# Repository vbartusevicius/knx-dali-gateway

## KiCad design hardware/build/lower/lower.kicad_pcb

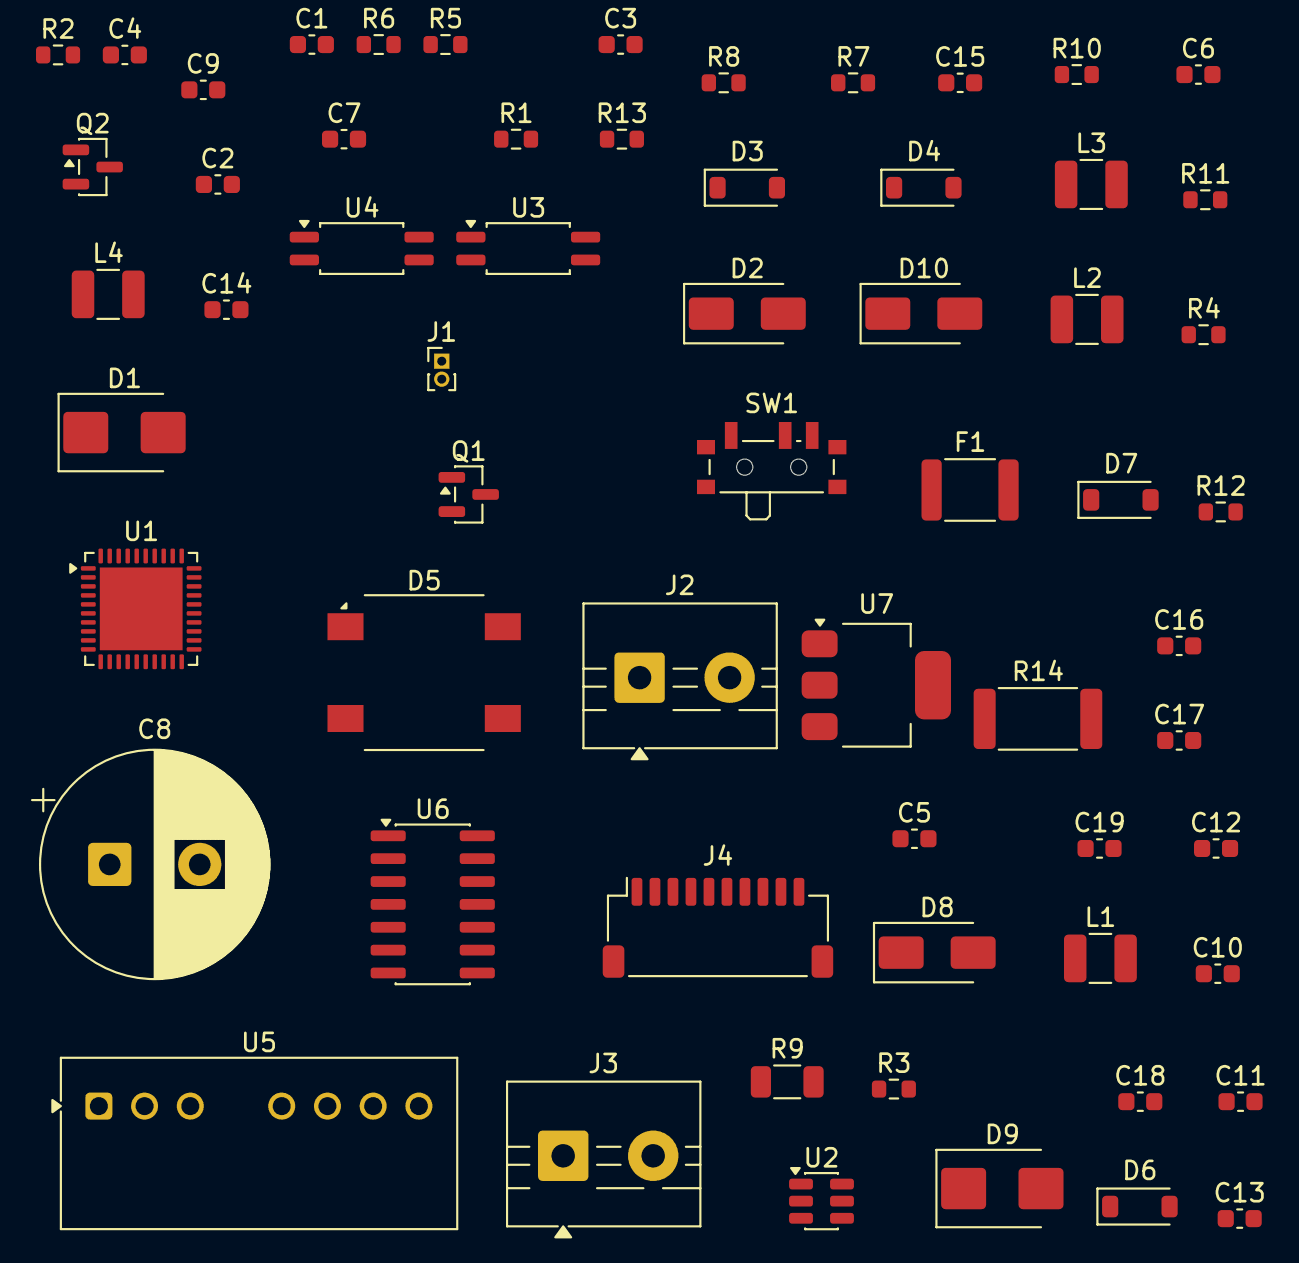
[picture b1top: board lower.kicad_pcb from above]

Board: 2 copper layers, 62 parts (0 on the bottom side), 46 nets, no tracks yet.

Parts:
C1, C3, C4: TBD; C_0603_1608Metric
C2, C6: TBD 1u; C_0603_1608Metric
C5, C16, C17, C18: TBD 10u; C_0603_1608Metric
C7: TBD 33u; C_0603_1608Metric
C8: 1000u 25V; CP_Radial_D12.5mm_P5.00mm
C9, C10, C12, C15: 100n; C_0603_1608Metric
C11: 10u; C_0603_1608Metric
C13, C14: 22u; C_0603_1608Metric
C19: TBD 100u; C_0603_1608Metric
D1: SMBJ33A TBD; D_SMB
D2, D8, D10: TBD 60V 1A; D_SMA
D3, D4: TBD 60V 1A; D_SOD-123
D5: TBD 600V 1A bridge; Diode_Bridge_Vishay_DFS
D6: TBD 12V; D_SOD-123
D7: TBD 8V2; D_SOD-123
D9: TBD ~36V; D_SMB
F1: TBD 250mA; Fuse_1812_4532Metric
J1: KNX bus terminal pins; PinHeader_1x02_P1.00mm_Vertical
J2: DALI; TerminalBlock_MaiXu_MX126-5.0-02P_1x02_P5.00mm
J3: AUX; TerminalBlock_MaiXu_MX126-5.0-02P_1x02_P5.00mm
J4: JST-SH 1x10; JST_SH_SM10B-SRSS-TB_1x10-1MP_P1.00mm_Horizontal
L1, L2: TBD 68uH; L_1210_3225Metric
L3: TBD 4.7uH; L_1210_3225Metric
L4: TBD 330uH; L_1210_3225Metric
Q1: TBD >=60V >=0.5A NMOS; SOT-23
Q2: TBD NPN; SOT-23
R1: TBD ~10k; R_0603_1608Metric
R2, R3, R12, R13: TBD; R_0603_1608Metric
R4: 100k; R_0603_1608Metric
R5: 1k; R_0603_1608Metric
R6, R11: 10k; R_0603_1608Metric
R7, R8: TBD 47k; R_0603_1608Metric
R9: 2R4 0.5W; R_1206_3216Metric
R10: TBD 10k; R_0603_1608Metric
R14: 5R 1W; R_2512_6332Metric
SW1: TBD slide SPDT; SW_SPDT_PCM12
U1: NCN5130MNTWG; QFN-40-1EP_6x6mm_P0.5mm_EP4.6x4.6mm
U2: AP63203WU-7; TSOT-23-6
U3, U4: TBD opto; SOP-4_4.4x2.6mm_P1.27mm
U5: TMR4-2425WI 24V->24V 4W iso; Converter_DCDC_TRACO_TMR4-xxxxWI_THT
U6: TBD LM2574HVM-ADJ; SOIC-14_3.9x8.7mm_P1.27mm
U7: TBD LM317; SOT-223-3_TabPin2

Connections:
+3V3_MCU: C13.1, C14.1, C15.1, J4.1, L3.2, R11.1, U2.1
+3V3_TRX: C7.1, L1.2, U1.19, U1.20, U1.29, U1.30, U1.40
+12V_STORE: C8.1, C9.1, C11.1, C12.1, L2.2, R2.1, R4.1, U1.12, U1.13, U2.3
AUX_FUSED: D8.1, F1.2
AUX_P: C16.1, D8.2, D9.2, U5.2
CAV: C2.1, U1.5
CCP: C1.1, U1.3
CCP_B: C1.2, U1.4
CEQ1: C3.1, U1.7
CEQ2: C4.1, U1.8
DA1: D5.3, J2.1, SW1.2
DA2: D5.4, J2.2
DALI_20V: C19.1, L4.2, R12.1, U7.3
DALI_FB6: R12.2, R13.1, U6.3
DALI_GATE: D6.1, Q1.1, Q2.3, R8.1, U3.3
DALI_ISO24V: C17.1, C18.1, U5.7, U6.10
DALI_RX: J4.7, R11.2, U4.4
DALI_SENSE: Q1.2, Q2.1, R9.1
DALI_SUPPLY_SW: R14.2, SW1.1, U7.1
DALI_TX: J4.6, R5.1, R6.1
DA_P: D5.1, Q1.3, R7.1, R10.1
GND: C2.2, C3.2, C4.2, C5.2, C6.2, C7.2, C8.2, C9.2, C11.2, C12.2, C13.2, C14.2, C15.2, D1.1, D3.1, D4.1, J1.2, J4.2, J4.5, J4.8, R1.2, R3.2, R6.2, U1.1, U1.2, U1.14, U1.18, U1.21, U1.23, U1.24, U1.25, U1.26, U1.31, U1.33, U2.4, U3.2, U4.3
GNDA: C16.2, D9.1, J3.2, U5.1
GNDD: C17.2, C18.2, C19.2, D5.2, D6.2, D10.1, Q2.2, R8.2, R9.2, R13.2, U4.2, U5.6, U6.4, U6.5, U6.6
INT_SPARE1: J4.9, U1.36
INT_SPARE2: J4.10, U1.37
KNX_P: D1.2, D2.2, J1.1
KNX_P_PROT: D2.1, U1.6
KNX_RXD: J4.4, U1.27
KNX_TXD: J4.3, U1.28
unnamed: R1.1, U1.38
unnamed: R4.2, U2.2
unnamed: C10.1, U2.6
unnamed: C10.2, L3.1, U2.5
unnamed: R5.2, U3.1
unnamed: R7.2, U3.4
unnamed: D7.1, R10.2
unnamed: D7.2, U4.1
unnamed: F1.1, J3.1
unnamed: D10.2, L4.1, U6.12
unnamed: R14.1, U7.2
V20V: C6.1, U1.10
VDD2MV: R2.2, R3.1, U1.11
VFILT: C5.1, U1.9, U1.16
VSW1: D3.2, L1.1, U1.17
VSW2: D4.2, L2.1, U1.15

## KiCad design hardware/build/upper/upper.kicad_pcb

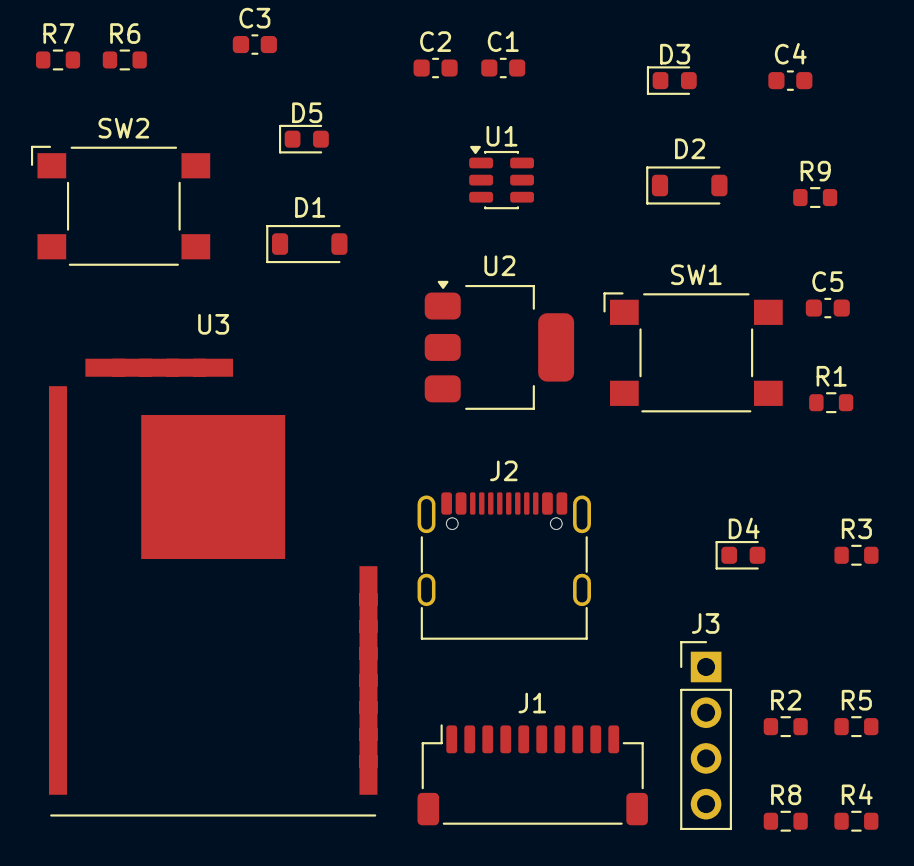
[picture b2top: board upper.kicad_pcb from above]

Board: 2 copper layers, 27 parts (0 on the bottom side), 22 nets, no tracks yet.

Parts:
C1, C5: 10u; C_0603_1608Metric
C2: 22u; C_0603_1608Metric
C3: 1u; C_0603_1608Metric
C4: 100n; C_0603_1608Metric
D1, D2: TBD 20V 1A; D_SOD-123
D3: red PROG; LED_0603_1608Metric
D4: green KNX; LED_0603_1608Metric
D5: yellow DALI; LED_0603_1608Metric
J1: JST-SH 1x10; JST_SH_SM10B-SRSS-TB_1x10-1MP_P1.00mm_Horizontal
J2: USB-C; USB_C_Receptacle_G-Switch_GT-USB-7010ASV
J3: OLED; PinHeader_1x04_P2.54mm_Vertical
R1, R2: 5.1k; R_0603_1608Metric
R3, R4: 10k; R_0603_1608Metric
R5, R6, R7: 1k; R_0603_1608Metric
R8, R9: 4.7k; R_0603_1608Metric
SW1: RESET; SW_SPST_Omron_B3FS-100xP
SW2: PROG; SW_SPST_Omron_B3FS-100xP
U1: TBD USB ESD; SOT-23-6
U2: TBD 3V3 LDO; SOT-223-3_TabPin2
U3: ESP32-C6-WROOM-1-N8; ESP32-C6-WROOM-1

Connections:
+3V3: C4.1, C5.1, D1.2, D2.2, J3.2, R3.1, R4.1, R8.1, R9.1, U3.2
+3V3_MCU: D2.1, J1.1
+3V3_USB: C2.1, D1.1, U2.2
+5V_USB: C1.1, J2.A4, J2.A9, J2.B4, J2.B9, U1.5, U2.3
DALI_RX: J1.7, U3.17
DALI_TX: J1.6, U3.16
EN: C3.1, R3.2, SW1.1, U3.3
GND: C1.2, C2.2, C3.2, C4.2, C5.2, D3.2, D4.2, D5.2, J1.2, J1.5, J1.8, J2.A1, J2.A12, J2.B1, J2.B12, J2.SH, J3.1, R1.2, R2.2, SW1.2, SW2.2, U1.2, U2.1, U3.1, U3.28, U3.29
I2C_SCL: J3.3, R9.2, U3.7
I2C_SDA: J3.4, R8.2, U3.6
INT_SPARE1: J1.9, U3.10
INT_SPARE2: J1.10, U3.9
KNX_RXD: J1.4, U3.19
KNX_TXD: J1.3, U3.18
unnamed: J2.A5, R1.1
unnamed: J2.B5, R2.1
unnamed: D3.1, R5.2
unnamed: D4.1, R6.2
unnamed: D5.1, R7.2
PROG_BTN: R4.2, SW2.1, U3.15
USB_DM: J2.A7, J2.B7, U1.1
USB_DP: J2.A6, J2.B6, U1.3

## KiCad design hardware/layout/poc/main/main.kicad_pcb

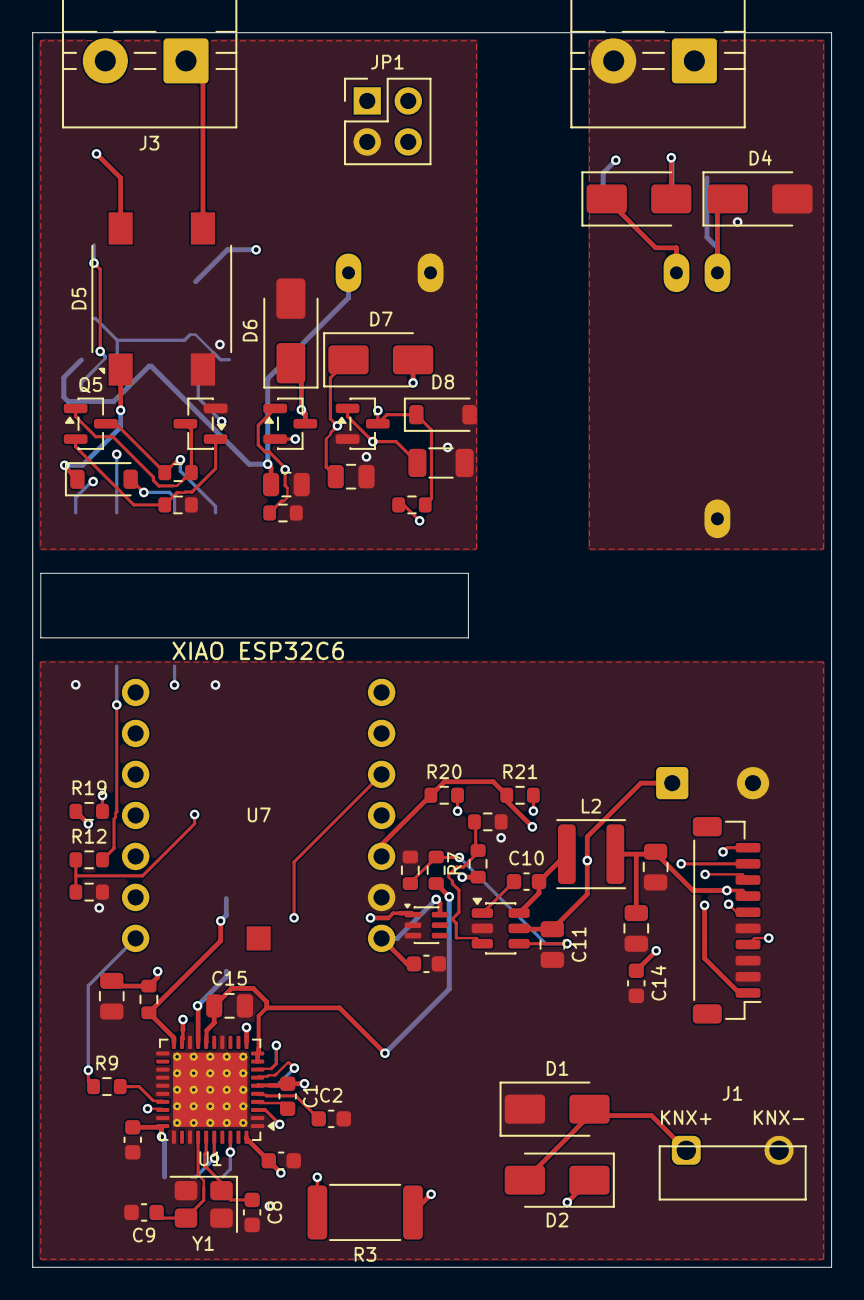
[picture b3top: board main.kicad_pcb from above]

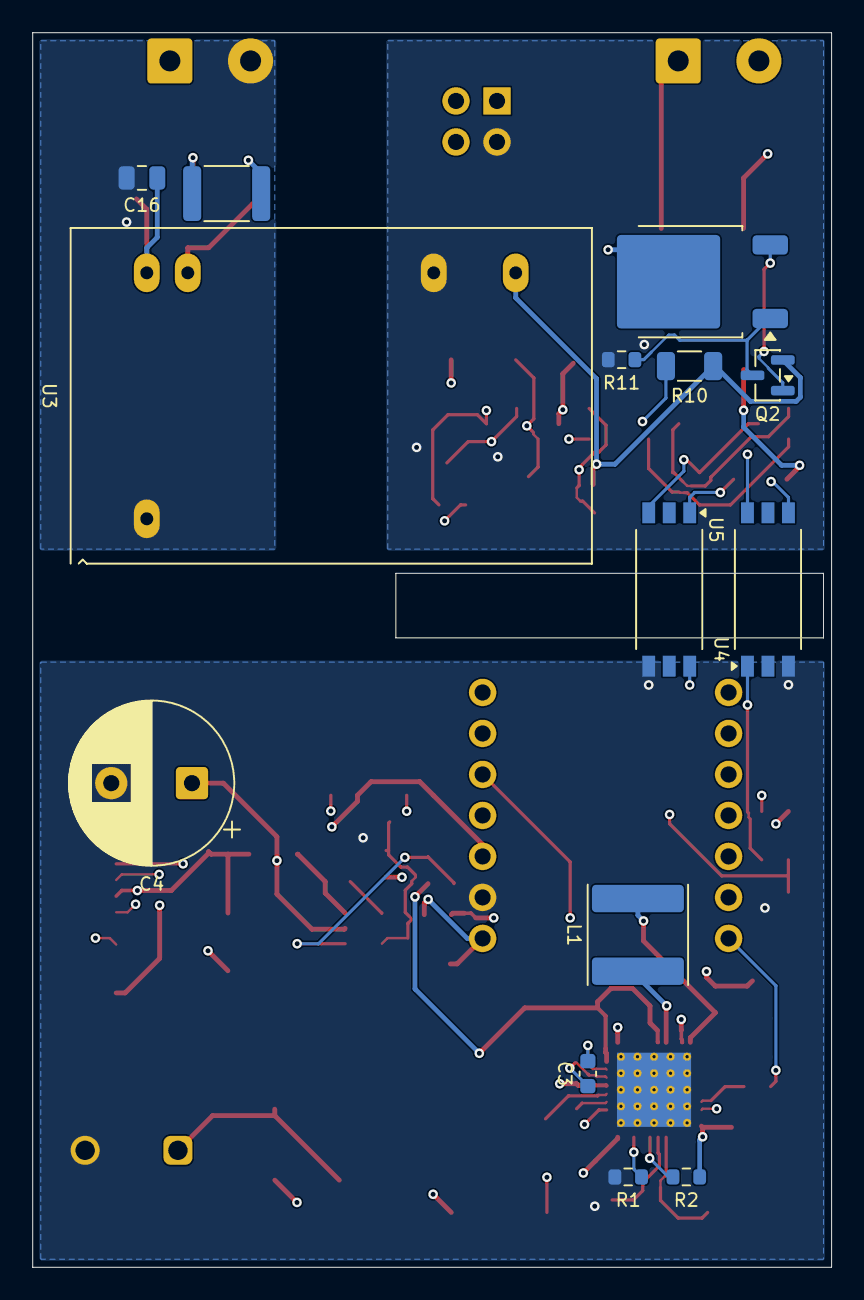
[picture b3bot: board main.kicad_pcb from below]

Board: 4 copper layers, 49.5 x 76.5 mm, 71 parts (14 on the bottom side), 54 nets.

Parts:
C1: 47n 50V; C_0603_1608Metric
C2, C5, C6, C10, C14: 100n 50V; C_0603_1608Metric
C3: 220n 50V; C_0603_1608Metric
C4: 470u 35V; CP_Radial_D10.0mm_P5.00mm
C7, C12, C13: 22u 25V; C_0805_2012Metric
C8, C9: 18p C0G 50V; C_0603_1608Metric
C11, C16: 10u 50V; C_0805_2012Metric
C15, C18: 1u 50V; C_0805_2012Metric
C17: 10u 25V; C_0805_2012Metric
C19: 10u 10V; C_0603_1608Metric
D1: SMAJ40CA; D_SMA
D2, D3, D7: SS16; D_SMA
D4: SMAJ33A; D_SMA
D5: DF06S; Diode_Bridge_Vishay_DFS
D6: SMAJ24A; D_SMA
D8: 12V; D_SOD-123
D9: 5V6; D_SOD-123
F1: 1.1A; Fuse_1812_4532Metric
J1: KNX bus terminal pins; Phoenix_PST_1,0-2-5,75_R32_1x02_P5.75mm
J2: AUX; TerminalBlock_MaiXu_MX126-5.0-02P_1x02_P5.00mm
J3: DALI; TerminalBlock_MaiXu_MX126-5.0-02P_1x02_P5.00mm
J4: JST-SH 1x10; JST_SH_BM10B-SRSS-TB_1x10-1MP_P1.00mm_Vertical
JP1: DALI supply; PinHeader_2x02_P2.54mm_Vertical
L1: 220uH; L_Sunlord_SWPA6045S
L2: 4.7uH; L_APV_ANR4012
Q1: MJD45H11; TO-252-2
Q2: BC857; SOT-23
Q3: IRLML0060; SOT-23
Q4, Q5, Q6: BC847; SOT-23
R1, R6, R8: 10k 1%; R_0603_1608Metric
R2, R13, R19: 10k; R_0603_1608Metric
R3: 27R; R_2512_6332Metric
R4: 1R; R_0603_1608Metric
R5: 120k 1%; R_0603_1608Metric
R7: 51k 1%; R_0603_1608Metric
R9: 1k; R_0603_1608Metric
R10, R16: 3R3; R_1206_3216Metric
R11, R20, R21: 4k7; R_0603_1608Metric
R12: 330R; R_0603_1608Metric
R14: 22k; R_0603_1608Metric
R15, R17: 100k; R_0603_1608Metric
R18: 680R; R_0603_1608Metric
U1: NCN5130MNTWG; QFN-40-1EP_6x6mm_P0.5mm_EP4.6x4.6mm_ThermalVias
U2: SCT2400TVBR; TSOT-23-6
U3: REM3-2415S/A 24V->15V 3W iso; Converter_DCDC_RECOM_REM3_DIP24
U4, U5: TLP383(D4BLLTL,E; SO-6L_10x3.84mm_P1.27mm
U6: LM66100; SOT-363_SC-70-6
U7: XIAO ESP32C6; XIAO_ESP32C6_Header
Y1: 16MHz; Crystal_SMD_3225-4Pin_3.2x2.5mm

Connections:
+3V3: J4.1, R19.1, R20.1, R21.1, U7.12
+3V3_TRX: C5.1, C6.1, C7.1, R2.1, R4.2, U1.11, U1.19, U1.30, U1.40
+5V: C12.1, C13.1, C14.1, J4.7, L2.2, R7.1, U6.1
+5V_XIAO: C19.1, U6.6, U7.14
AUX_FUSED: D3.2, F1.2
AUX_P: C16.1, D3.1, D4.1, U3.22, U3.23
BTN_LADDER: J4.4, U7.3
CAV: C2.1, U1.5
CCP: C1.2, U1.4
CEQ1: C3.1, U1.7
CEQ2: C3.2, U1.8
DA1: D5.3, J3.1, JP1.2
DA2: D5.4, J3.2, JP1.4
DALI_BOOT: C18.1, D7.1, U4.6
DALI_GATE: D8.1, Q3.1, Q4.3, R14.2, R15.1
DALI_GATE_SW: R14.1, U4.4
DALI_ISO15V: C17.1, Q2.2, R10.1, U3.14
DALI_RX: R19.2, U5.6, U7.9
DALI_SENSE: Q3.2, Q4.1, R16.1
DALI_SUPPLY_SW: JP1.1, Q1.2
DALI_TX: R12.1, R13.1, U7.11
DA_P: D5.1, D6.1, D7.2, D9.1, Q3.3
FANIN: R1.1, U1.38
GND: C2.2, C4.2, C5.2, C6.2, C7.2, C8.2, C9.2, C11.2, C12.2, C13.2, C14.2, C15.2, C19.2, D1.1, J1.2, J4.2, J4.3, J4.5, R1.2, R6.2, R8.2, R13.2, U1.1, U1.2, U1.14, U1.18, U1.21, U1.23, U1.24, U1.25, U1.26, U1.29, U1.31, U1.33, U1.41, U2.2, U4.3, U5.4, U6.2, U6.3, U7.13, Y1.2, Y1.4
GNDA: C16.2, D4.2, J2.2, U3.2
GNDD: C17.2, C18.2, D5.2, D6.2, D8.2, JP1.3, Q4.2, Q6.2, R11.2, R15.2, R16.2, R18.2, U3.16
I2C_SCL: J4.10, R21.2, U7.6
I2C_SDA: J4.9, R20.2, U7.5
KNX_P: D1.2, D2.2, J1.1
KNX_P_PROT: C1.1, D2.1, R3.1, U1.6
KNX_RXD: R9.1, U7.7
KNX_TXD: U1.28, U7.8
LED_DALI: J4.8, U7.4
LED_DATA: J4.6, U7.1
unnamed: R5.2, R6.1, U2.4
unnamed: C10.1, U2.1
unnamed: R7.2, R8.1, U2.3
unnamed: R9.2, U1.27
unnamed: F1.1, J2.1
unnamed: Q1.3, Q2.1, R10.2
unnamed: Q1.1, Q2.3, R11.1
unnamed: R12.2, U4.1
unnamed: D9.2, U5.1
unnamed: Q5.2, Q6.1, R18.1
unnamed: Q5.1, Q6.3, R17.2
NCN_SAVEB: R2.2, U1.36, U7.10
RX_LIM_IN: Q5.3, R17.1, U5.3
SW: C10.2, L2.1, U2.6
TX0: R3.2, U1.3
VDD1M: L1.2, R4.1, U1.20
VFILT: C4.1, C11.1, C15.1, R5.1, U1.9, U1.10, U1.16, U2.5
VSW1: L1.1, U1.17
XTAL1: C8.1, U1.35, Y1.1
XTAL2: C9.1, U1.34, Y1.3

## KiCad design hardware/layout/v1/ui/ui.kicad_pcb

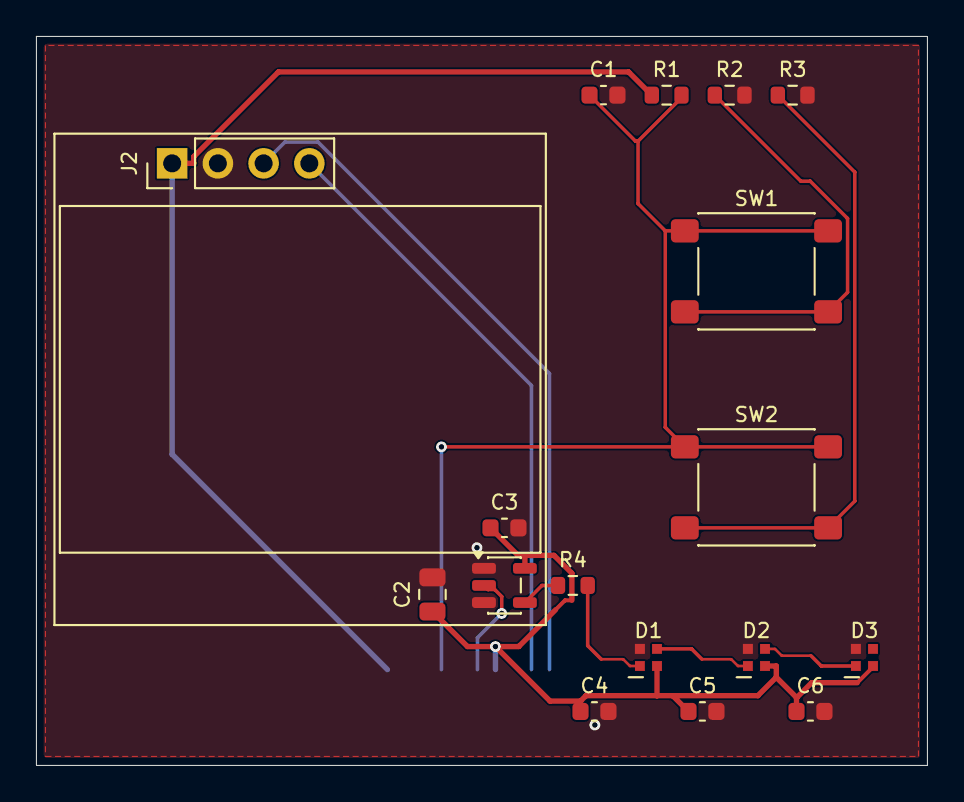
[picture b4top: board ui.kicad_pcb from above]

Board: 2 copper layers, 49.5 x 40.5 mm, 18 parts (1 on the bottom side), 13 nets.

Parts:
C1, C3, C4, C5, C6: 100n 50V; C_0603_1608Metric
C2: 1u 50V; C_0805_2012Metric
D1: RGB STATUS; LED_SK6805-EC15_1.5x1.5mm
D2: RGB KNX; LED_SK6805-EC15_1.5x1.5mm
D3: RGB DALI; LED_SK6805-EC15_1.5x1.5mm
J1: JST-SH 1x10; JST_SH_BM10B-SRSS-TB_1x10-1MP_P1.00mm_Vertical
J2: OLED; PinHeader_1x04_P2.54mm_Vertical
R1, R3: 10k; R_0603_1608Metric
R2: 20k; R_0603_1608Metric
R4: 330R; R_0603_1608Metric
SW1: PRG/RST; SW_SPST_PTS645Sx43SMTR92
SW2: FUNC; SW_SPST_PTS645Sx43SMTR92
U1: 74AHCT1G125; SOT-23-5

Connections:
+3V3: J1.1, J2.1, R1.1
+5V: C2.1, C3.1, C4.1, C5.1, C6.1, D1.2, D2.2, D3.2, J1.7, U1.5
BTN_LADDER: C1.1, J1.4, R1.2, SW1.1, SW2.1
GND: C1.2, C2.2, C3.2, C4.2, C5.2, C6.2, D1.4, D2.4, D3.4, J1.2, J1.3, J1.5, J1.8, J2.2, R2.2, R3.2, U1.1, U1.3
I2C_SCL: J1.10, J2.3
I2C_SDA: J1.9, J2.4
LED_CHAIN1: D1.3, D2.1
LED_CHAIN2: D2.3, D3.1
LED_DATA: J1.6, U1.2
unnamed: R2.1, SW1.2
unnamed: R3.1, SW2.2
unnamed: R4.1, U1.4
unnamed: D1.1, R4.2

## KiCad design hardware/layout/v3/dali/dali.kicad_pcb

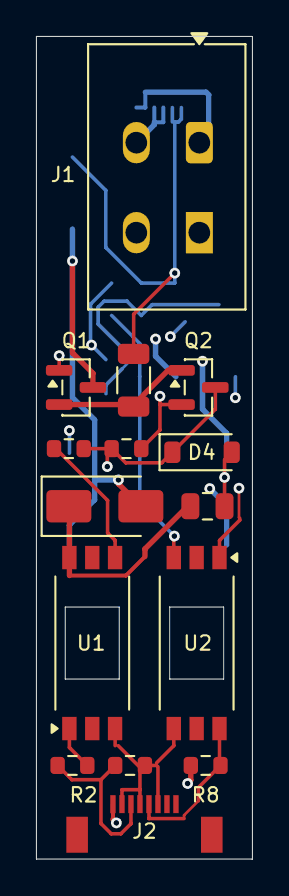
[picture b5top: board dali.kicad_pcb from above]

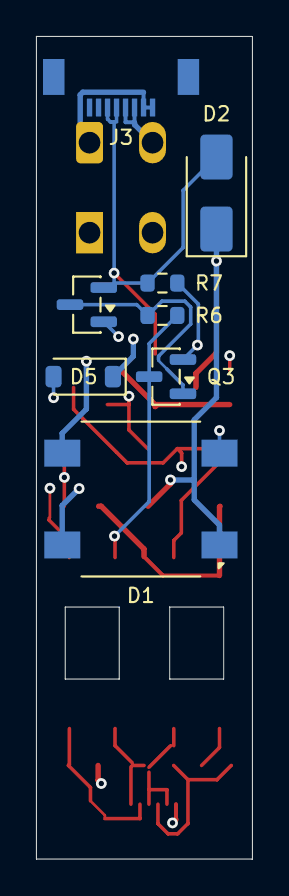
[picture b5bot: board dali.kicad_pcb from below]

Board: 4 copper layers, 12.0 x 45.7 mm, 23 parts (8 on the bottom side), 17 nets.

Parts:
C1: 1u 50V; C_0805_2012Metric
D1: DF06S; Diode_Bridge_Vishay_DFS
D2: SMAJ24A; D_SMA
D3: SS16; D_SMA
D4: 12V; D_SOD-123
D5: 5V6; D_SOD-123
J1: DALI; TerminalBlock_WAGO_2601-1102_1x02_P3.50mm_Horizontal
J2: Carrier logic; FPC_Kinghelm_KH-FPC0.5-H1.2SMT-8P
J3: Carrier bus; FPC_Kinghelm_KH-FPC0.5-H1.2SMT-8P
Q1: IRLML0060; SOT-23
Q2, Q3, Q4: BC847; SOT-23
R1: 330R; R_0603_1608Metric
R2, R8: 10k; R_0603_1608Metric
R3: 22k; R_0603_1608Metric
R4, R6: 100k; R_0603_1608Metric
R5: 3R3; R_1206_3216Metric
R7: 680R; R_0603_1608Metric
U1, U2: TLP383(D4BLLTL,E; SO-6L_10x3.84mm_P1.27mm

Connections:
+3V3: J2.1, R8.1
DA1: D1.3, J1.1, J3.1, J3.2
DA2: D1.4, J1.2, J3.3, J3.4
DALI_BOOT: C1.1, D3.1, U1.6
DALI_GATE: D4.1, Q1.1, Q2.3, R3.2, R4.1
DALI_GATE_SW: R3.1, U1.4
DALI_RX: J2.5, R8.2, U2.6
DALI_SENSE: Q1.2, Q2.1, R5.1
DALI_TX: J2.3, R1.1, R2.1
DA_P: D1.1, D2.1, D3.2, D5.1, Q1.3
GND: J2.2, J2.4, J2.6, R2.2, U1.3, U2.4
GNDD: C1.2, D1.2, D2.2, D4.2, J3.5, J3.6, Q2.2, Q4.2, R4.2, R5.2, R7.2
unnamed: R1.2, U1.1
unnamed: D5.2, U2.1
unnamed: Q3.2, Q4.1, R7.1
unnamed: Q3.1, Q4.3, R6.2
RX_LIM_IN: Q3.3, R6.1, U2.3
